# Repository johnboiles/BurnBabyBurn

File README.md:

BurnBabyBurn
============
http://github.com/johnboiles/BurnBabyBurn

Tiny board for controlling a high-power logic-level n-channel MOSFET transistor. Useful for burning stuff (like nichrome wire). Can be used as a timed cut-off for high-altitude ballooning.

Firmware
--------
Firmware is designed for the [Sparkfun Arduino Pro Micro](https://www.sparkfun.com/products/11098). It is extremely simple, and should be compatible with any arduino board.

PCB
---
The PCB is also designed for a [Sparkfun Arduino Pro Micro](https://www.sparkfun.com/products/11098), though I'm confident it could be used with a [Arduino Pro Mini](http://arduino.cc/en/Main/ArduinoBoardProMini).

Bill of Materials
-----------------
2x [Screw Terminals 3.5mm Pitch (2-Pin)](https://www.sparkfun.com/products/8084)

1x [N-Channel Mosfet](https://www.sparkfun.com/products/10213)

1x [Arduino Pro Micro](https://www.sparkfun.com/products/11098)

1x [Female Headers](https://www.sparkfun.com/products/115)

1x [Break Away Headers](https://www.sparkfun.com/products/116)

1x 10 kOhm Resistor

1x 220 Ohm Resistor

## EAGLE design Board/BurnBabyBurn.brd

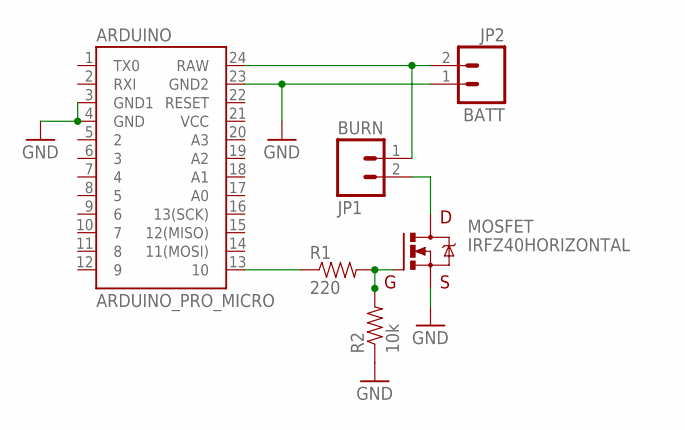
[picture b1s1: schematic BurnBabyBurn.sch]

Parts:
ARDUINO: ARDUINO_PRO_MICRO
JP1: BURN; SCREWTERMINAL-3.5MM-2
JP2: BATT; SCREWTERMINAL-3.5MM-2
MOSFET: IRFZ40HORIZONTAL; TO220
R1: 220; AXIAL-0.3EZ
R2: 10k; AXIAL-0.3EZ

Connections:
GND: ARDUINO.3 (GND1), ARDUINO.4 (GND), ARDUINO.23 (GND2), JP2.1, MOSFET.3 (S), R2.P$1 (1)
unnamed: MOSFET.1 (G), R1.P$2 (2), R2.P$2 (2)
unnamed: JP1.2, MOSFET.2 (D)
unnamed: ARDUINO.13 (10), R1.P$1 (1)
VBATT: ARDUINO.24 (RAW), JP1.1, JP2.2

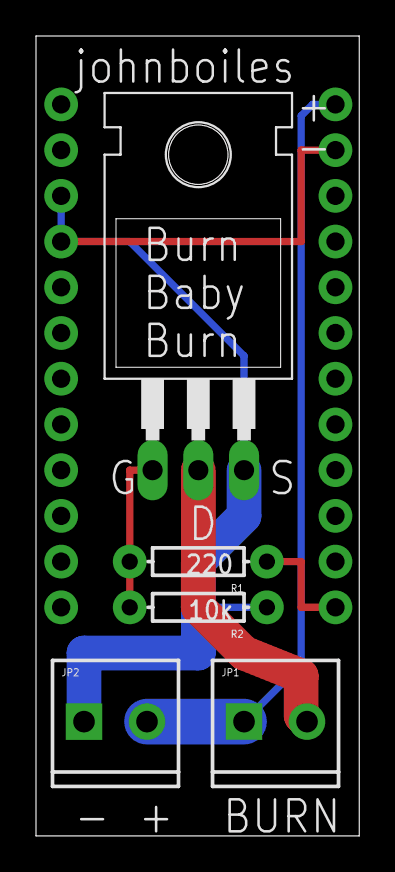
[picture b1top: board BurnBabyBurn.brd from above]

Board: 2 copper layers, 18.0 x 44.4 mm, 6 parts (0 on the bottom side), 5 nets.

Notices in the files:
parts and their libraries:
SparkFun-Boards: Licensing: CC v3.0 Share-Alike You are welcome to use this library for commercial purposes.
